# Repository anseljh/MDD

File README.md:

# Mouse Deterrent Device

A mouse decided it liked the space under the hood of my car. Supposedly, they don't like ultraviolet light, so I designed a small device that could go in there to deter critters from settling in at night.

## What it does

- Connects to home wifi
- Gets the current time via NTP
- Gets sunrise and sunset times from the [SunriseSunset.io](https://sunrisesunset.io/) API
- If it's daytime, goes into battery-saving deep sleep until sunset
- If it's night, light the UV LED, and go into a lighter sleep mode until sunrise to save some battery

## Hardware

- [Seeed Studio XIAO ESP32-C6](https://www.seeedstudio.com/Seeed-Studio-XIAO-ESP32C6-p-5884.html)
- A battery (soldered to pads on Xiao) or USB battery pack
- Ultraviolet LED (like [this one](https://www.jameco.com/webapp/wcs/stores/servlet/ProductDisplay?catalogId=10001&langId=-1&storeId=10001&productId=2274823))
- Resistor appropriate for your UV LED (4.7 Ω for the one linked above)

## Circuit schematics and PCB

PCB design files for [KiCad](https://www.kicad.org/) are in `PCB` folder.

(This render shows a slightly different Xiao board, not the ESP32-C6 version.)

[Mouse image](https://thenounproject.com/icon/mouse-7950563/) by Kim Sun Young from [Noun Project](https://thenounproject.com/browse/icons/term/mouse/) ([CC BY 3.0](https://creativecommons.org/licenses/by/3.0/)).

## Software

- [CircuitPython](https://circuitpython.org/)
  - [adafruit_connection_manager](https://docs.circuitpython.org/projects/connectionmanager/en/latest/index.html)
  - [adafruit_ntp](https://docs.circuitpython.org/projects/ntp/en/latest/index.html)
  - [adafruit_requests](https://docs.circuitpython.org/projects/requests/en/latest/index.html)
- Powered by [SunriseSunset.io](https://sunrisesunset.io/)'s sunrise/sunset API.

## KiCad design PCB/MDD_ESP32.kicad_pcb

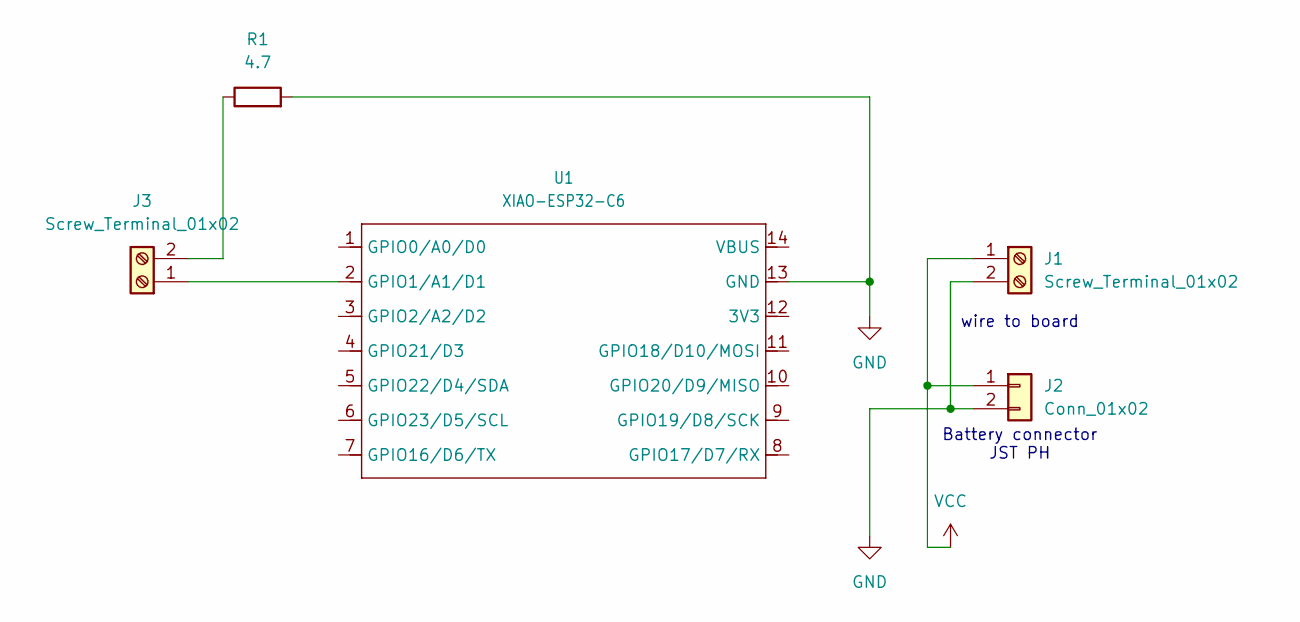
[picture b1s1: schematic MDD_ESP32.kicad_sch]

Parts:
J1, J3: Screw_Terminal_01x02; TerminalBlock_Phoenix_MPT-0,5-2-2.54_1x02_P2.54mm_Horizontal
J2: Conn_01x02; JST_PH_B2B-PH-K_1x02_P2.00mm_Vertical
R1: 4.7; R_Axial_DIN0204_L3.6mm_D1.6mm_P7.62mm_Horizontal
U1: XIAO-ESP32-C6; XIAO-ESP32C6-DIP

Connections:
GND: J1.2, J2.2, R1.2, U1.13 (GND)
unnamed: J3.1, U1.2 (GPIO1/A1/D1)
unnamed: J3.2, R1.1
VCC: J1.1, J2.1

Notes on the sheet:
Battery connector JST PH
wire to board

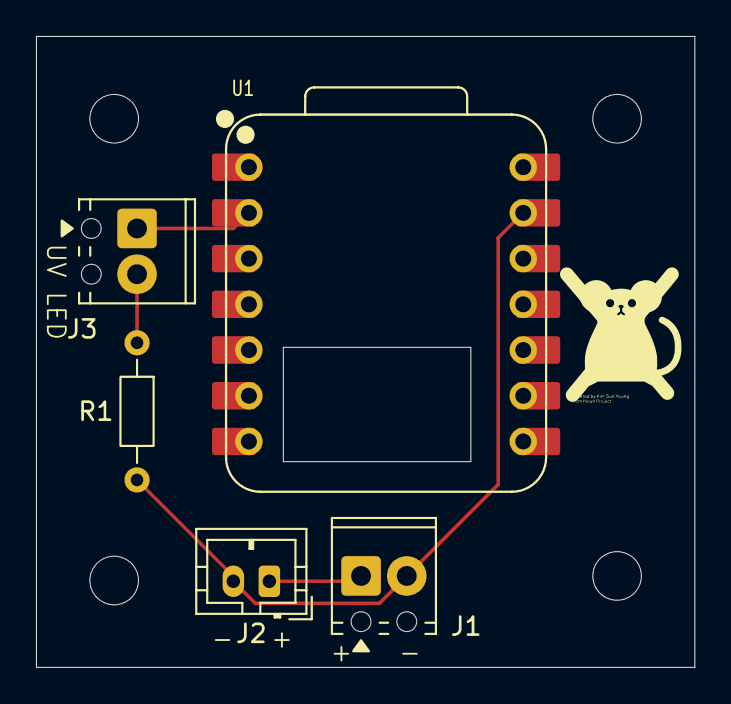
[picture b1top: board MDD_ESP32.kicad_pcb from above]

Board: 2 copper layers, 36.6 x 35.1 mm, 5 parts (0 on the bottom side), 4 nets.

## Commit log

2025-09-02 Checkpoint
2025-09-02 Cleanup
2025-09-02 Remove unused import
2025-09-05 Use env vars for config; aesthetic improvements
2025-09-05 Move code around; clean up; add to README
2025-09-07 Run black formatter
2025-09-07 Add KiCAD PCB files
2025-09-07 Expanded discussion in README.md
2025-09-07 Add PCB render
2025-09-14 Change UV LED pin from D1 to D0
2025-09-14 Give lat/long as strings in settings.toml
2025-09-14 Add logging to Adafruit.io
